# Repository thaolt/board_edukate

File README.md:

# board_edukate

CHIP8 emulation board for education purpose (edu-c8) based on STM32F103VET6

Designed in KiCad 5.1

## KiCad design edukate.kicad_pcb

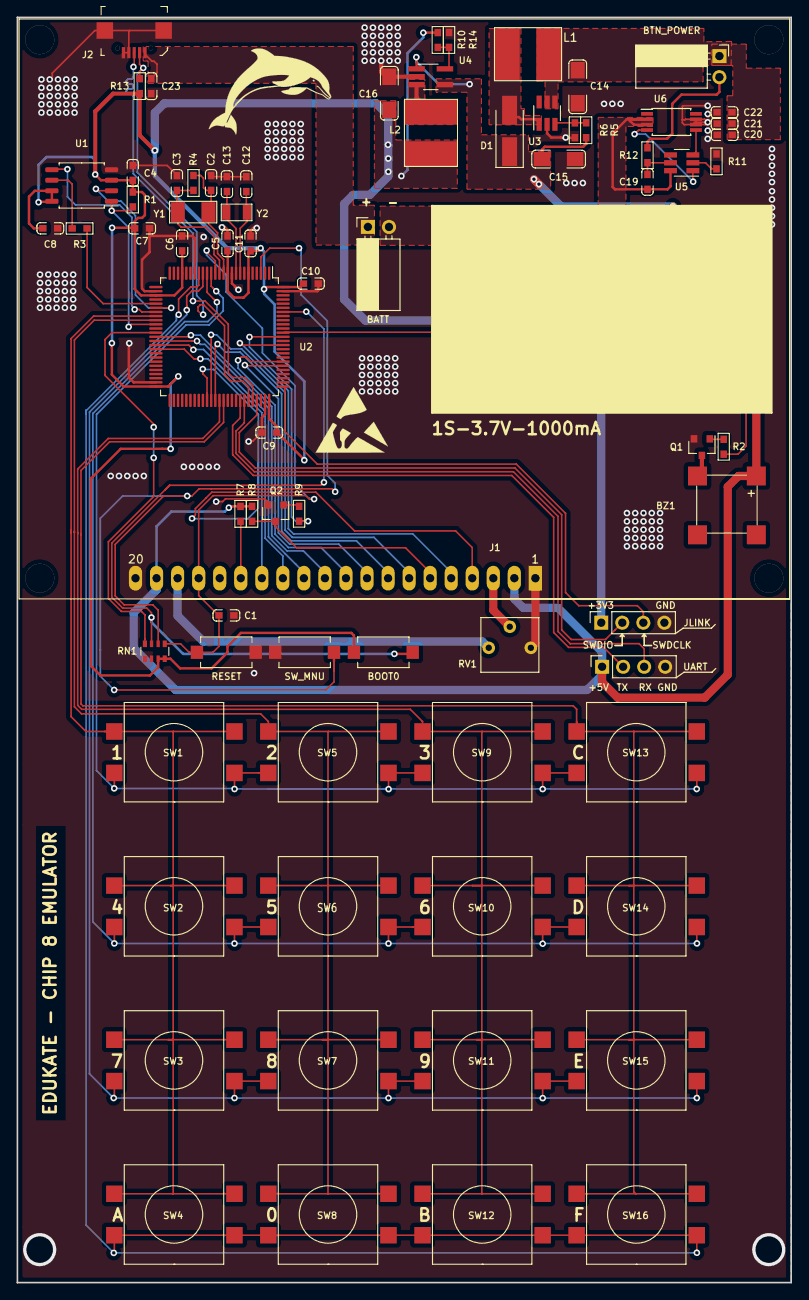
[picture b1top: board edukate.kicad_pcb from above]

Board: 2 copper layers, 93.4 x 152.7 mm, 76 parts (0 on the bottom side), 60 nets.

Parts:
BATT: Battery_Cell; PinSocket_1x02_P2.54mm_Horizontal
BOOT0: SW_SPST; SW_3x6x5_2Pin_SMD
BTN_POWER: SW_SPST; PinSocket_1x02_P2.54mm_Horizontal
BZ1: Buzzer; BUZZER MLT-8530
C1, C4, C5, C6, C7, C8, C9, C10, C19, C20: 104; C0603_HandSoldering
C2, C3: 22P; C0603_HandSoldering
C11: 106; C0603_HandSoldering
C12, C13: 12P; C0603_HandSoldering
C14, C15, C16: C1206/22uF/16V; C1206_HandSoldering
C21, C22, C23: 10u; C0603_HandSoldering
D1: SS34; D_SMA_Handsoldering
J1: Conn_LCD; GraphicLCD_128x44(ST7920)
J2: USB_OTG; USB_Micro_B_Female_SMD
JLINK: Conn_JLINK; PinSocket_1x04_P2.54mm_Vertical
L1: 5D28/10uH/1.5A; INDUCTOR 5D28-5D18
L2: 5D28/2.2uH/1A; INDUCTOR 5D28-5D18
Q1, Q2: C1815; SOT-23
R1, R8: 10K; R0603_HandSoldering
R2, R7, R9, R11: 1K; R0603_HandSoldering
R3: 22R; R0603_HandSoldering
R4: 1M; R0603_HandSoldering
R5: 150K; R0603_HandSoldering
R6: 20K; R0603_HandSoldering
R10: 15K; R0603_HandSoldering
R12: 100; R0603_HandSoldering
R13: 1.5K; R0603_HandSoldering
R14: 3.3K; R0603_HandSoldering
RESET: SW_SPST; SW_3x6x5_2Pin_SMD
RN1: R_Pack04/10K; R_Array_Convex_4x0603
RV1: R_POT/10K; 3362_potentiometer
SW1: KEY 1; BUTTON 12X12 4PIN SMD
SW2: KEY 4; BUTTON 12X12 4PIN SMD
SW3: KEY 7; BUTTON 12X12 4PIN SMD
SW4: KEY A; BUTTON 12X12 4PIN SMD
SW5: KEY 2; BUTTON 12X12 4PIN SMD
SW6: KEY 5; BUTTON 12X12 4PIN SMD
SW7: KEY 8; BUTTON 12X12 4PIN SMD
SW8: KEY 0; BUTTON 12X12 4PIN SMD
SW9: KEY 3; BUTTON 12X12 4PIN SMD
SW10: KEY 6; BUTTON 12X12 4PIN SMD
SW11: KEY 9; BUTTON 12X12 4PIN SMD
SW12: KEY B; BUTTON 12X12 4PIN SMD
SW13: KEY C; BUTTON 12X12 4PIN SMD
SW14: KEY D; BUTTON 12X12 4PIN SMD
SW15: KEY E; BUTTON 12X12 4PIN SMD
SW16: KEY F; BUTTON 12X12 4PIN SMD
SW_MNU: SW_SPST; SW_3x6x5_2Pin_SMD
U1: W25Q16DVSS; SOIC-8_5.23x5.23mm_P1.27mm
U2: STM32F103VET6; LQFP-100_14x14mm_P0.5mm
U3: SX1308; SOT-23-6_Handsoldering
U4: NCP1529; TSOT-23-5_HandSoldering
U5: DW01A; SOT-23-6_Handsoldering
U6: FS8205A; TSSOP-8_4.4x3mm_P0.65mm
UART: Conn_ISP; PinSocket_1x04_P2.54mm_Vertical
Y1: 8M; CRYSTAL 5032-2PIN
Y2: 32.768K; CRYSTAL CC7V-T1A 32.768KHz (3215)

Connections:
+3V3: BOOT0.1, C4.1, C5.1, C6.1, C7.1, C8.1, C9.1, C10.1, C11.1, C16.1, JLINK.1, L2.2, R1.1, R10.2, R13.1, RN1.3, RN1.4, U1.3, U1.7, U1.8, U2.6, U2.11, U2.22, U2.28, U2.50, U2.75, U2.100
+5V: BZ1.1, C15.1, D1.1, J1.2, J1.19, R5.2, R7.1, R8.1, U4.1, U4.4, UART.1
+BATT: BATT.1, BTN_POWER.2, C23.1, J2.1, R12.2
+VSW: BTN_POWER.1, C14.1, C20.1, C21.1, C22.1, L1.1, U3.4, U3.5
-BATT: BATT.2, C19.2, U5.6, U6.2, U6.3
/BOOT0: BOOT0.2, RN1.7, U2.94
/BOOT1: RN1.8, U2.37
/BUZZ_PIN: R2.1, U2.89
/FLASH_CS: R1.2, U1.1, U2.35
/FSMC_NE1: R9.1, U2.88
/FSMC_NWE: J1.5, U2.86
/KP_C1: SW1.1, SW2.1, SW3.1, SW4.1, U2.33
/KP_C2: SW5.1, SW6.1, SW7.1, SW8.1, U2.34
/KP_C3: SW9.1, SW10.1, SW11.1, SW12.1, U2.63
/KP_C4: SW13.1, SW14.1, SW15.1, SW16.1, U2.64
/KP_R1: SW1.2, SW5.2, SW9.2, SW13.2, U2.15
/KP_R2: SW2.2, SW6.2, SW10.2, SW14.2, U2.16
/KP_R3: SW3.2, SW7.2, SW11.2, SW15.2, U2.17
/KP_R4: SW4.2, SW8.2, SW12.2, SW16.2, U2.18
/LCD_DB0: J1.7, U2.61
/LCD_DB1: J1.8, U2.62
/LCD_DB2: J1.9, U2.81
/LCD_DB3: J1.10, U2.82
/LCD_DB4: J1.11, U2.38
/LCD_DB5: J1.12, U2.39
/LCD_DB6: J1.13, U2.40
/LCD_DB7: J1.14, U2.41
/LCD_EN: J1.6, Q2.3, R8.2
/LCD_PSB: J1.15, R7.2
/LCD_RS: J1.4, U2.60
/LCD_RST: C1.2, J1.17, RESET.2, RN1.5, U2.14
/LCD_V0: J1.3, RV1.2
/LCD_VOUT: J1.18, RV1.3
/OSC32_IN(PC14): C12.1, U2.8, Y2.2
/OSC32_OUT(PC15): C13.2, U2.9, Y2.1
/SPI1_CLK: R3.1, U2.30
/SPI1_MISO: U1.2, U2.31
/SPI1_MOSI: U1.5, U2.32
/SWDCLK: JLINK.3, U2.76
/SWDIO: JLINK.2, U2.72
/SW_MNU: RN1.6, SW_MNU.2, U2.3
/UART1_RX(PA10): U2.69, UART.3
/UART1_TX(PA9): U2.68, UART.2
/USB_DM(PA11): J2.2, R13.2, U2.70
/USB_DP(PA12): J2.3, U2.71
Earth: C1.1, C2.1, C3.2, C4.2, C5.2, C6.2, C7.2, C8.2, C9.2, C10.2, C11.2, C12.2, C13.1, C14.2, C15.2, C16.2, C20.2, C21.2, C22.2, C23.2, J1.1, J1.20, J2.4, J2.5, J2.6, JLINK.4, Q1.2, Q2.2, R6.1, R11.2, R14.1, RESET.1, RN1.1, RN1.2, RV1.1, SW_MNU.1, U1.4, U2.10, U2.19, U2.27, U2.49, U2.74, U2.99, U3.2, U4.2, U6.6, U6.7, UART.4
unnamed: BZ1.2, Q1.3
unnamed: C2.2, R4.1, U2.12, Y1.1
unnamed: C3.1, R4.2, U2.13, Y1.2
unnamed: C19.1, R12.1, U5.5
unnamed: D1.2, L1.2, U3.1
unnamed: L2.1, U4.3
unnamed: Q1.1, R2.2
unnamed: Q2.1, R9.2
unnamed: R3.2, U1.6
unnamed: R5.1, R6.2, U3.3
unnamed: R10.1, R14.2, U4.5
unnamed: R11.1, U5.2
unnamed: U5.1, U6.4
unnamed: U5.3, U6.5

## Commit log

2019-06-07 initial import
2019-06-07 update schematic
2019-06-08 add datasheets of applied components
2019-06-08 create new symbols for battery management
2019-06-08 add buzzer circuit
2019-06-08 battery charger circuit
2019-06-09 complete lcd interface connection
2019-06-09 added appnote of stm32 interface lcd through fsmc, added st7920 datasheet
2019-06-09 deleted erc markers
2019-06-09 create project blank footprint library
2019-06-10 import help re-organizing from @thiennhan92
2019-06-10 add some dirty edit of symbols to pass ERC
2019-06-26 add 0.9v to 5v boot module
2019-07-25 update boost and buck module, add keypad module
2019-07-26 assign footprint
2019-07-29 update components position in pcb layout
2019-07-30 finished pcb layout
2019-07-31 add schematic in pdf
2019-10-16 update rawBOM list
